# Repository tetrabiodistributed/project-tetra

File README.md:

# Project Tetra - Project Repository
This repository contains STL files and schematics for Project Tetra.

Project documentation available at https://tetrabiodistributed.github.io/docs

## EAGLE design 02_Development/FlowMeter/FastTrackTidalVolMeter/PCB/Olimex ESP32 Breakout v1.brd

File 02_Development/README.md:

READ ME

File for designs of the part in all stages, 
draft, final, in testing, 

PLEASE LABEL THE DESIGNS WITH THE STATUS AND VERSION.

PLEASE CREATE A PULL REQUEST FOR EACH DESIGN OF SPLITTER

MAIN FOCUS:

TEST RESULTS NEEDED

dimensions of tubing, if they fit

strength

flow

test with different lung sizes and compliances

flow rates to diff patients

TO DESIGN ensure fittings are ISO

device at the mouth to measure tidal flow, pressure,tidal volume

antiviral & antibacterial filter - integrated into design but not essential for operation

regulator of max pressure into lungs

PEEP valve connector

3 way valve formpatiemt isolation

On git with files please create a text/pdf documentation

Thread specs: ALL IN 3/8" NPT PLEASE

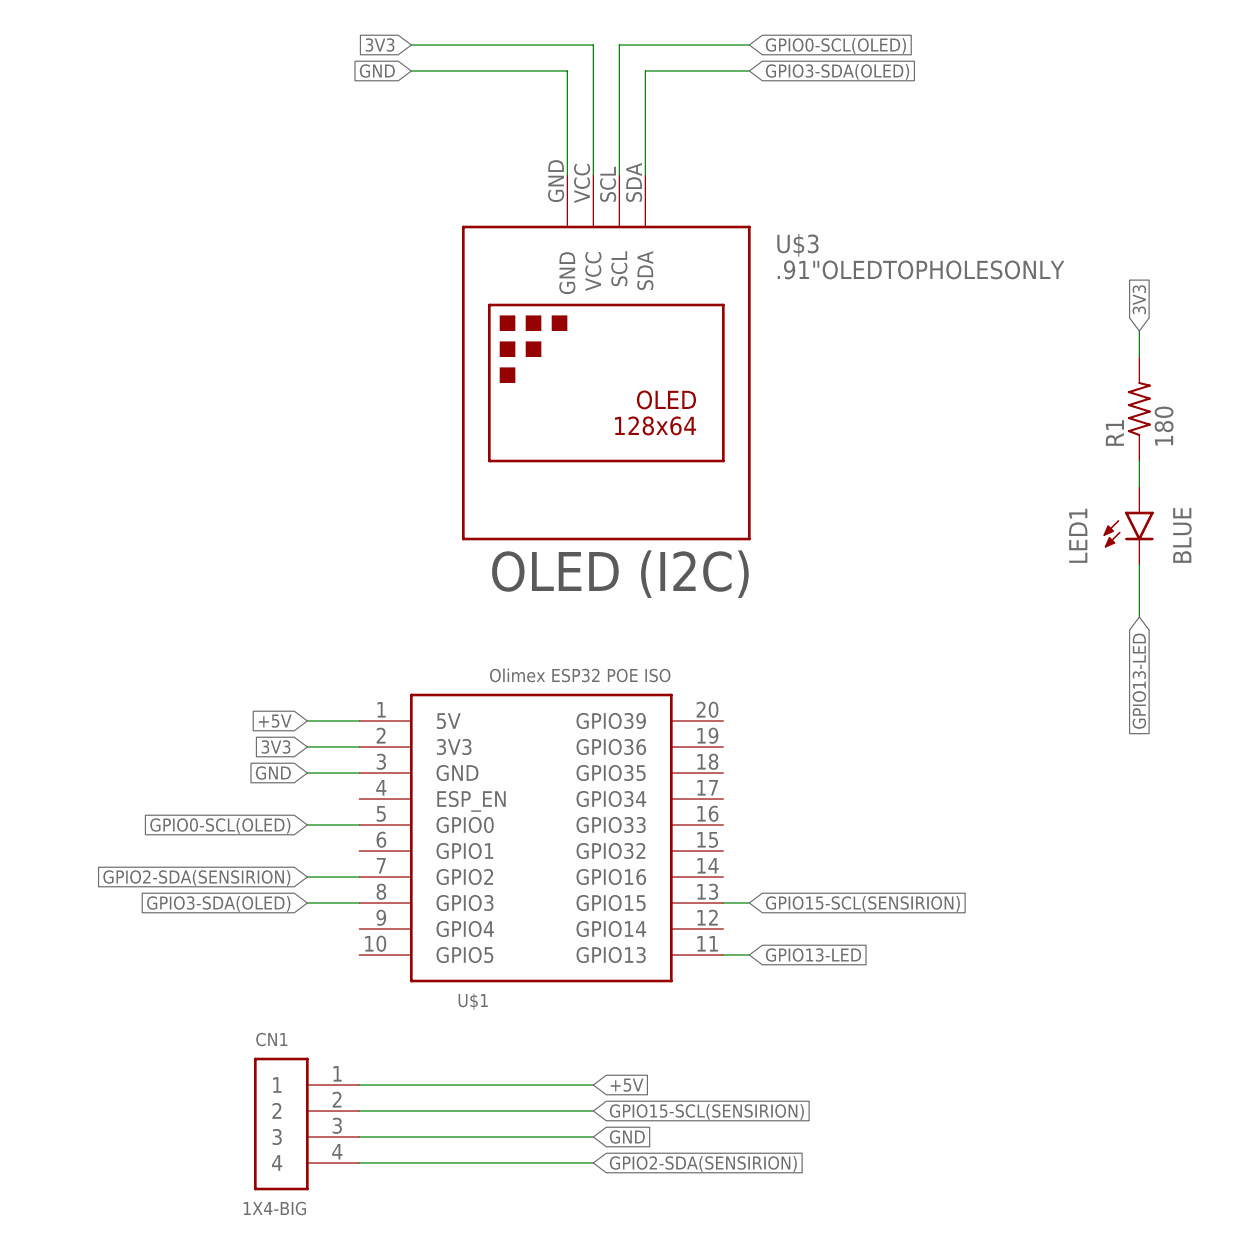
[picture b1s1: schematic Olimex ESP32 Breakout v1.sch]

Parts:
CN1: 1X4-BIG; 1X04-BIG
LED1: BLUE; LED-1206
R1: 180; R0805
U$1: OLIMEX_POE_ISOPOEISO; OLIMEX_POE_ISO
U$3: .91"OLEDTOPHOLESONLY; .96"OLED-TOPHOLESONLY

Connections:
3V3: R1.2, U$1.2 (3V3), U$3.VCC
+5V: CN1.1, U$1.1 (5V)
BLUEX: LED1.A, R1.1
GND: CN1.3, U$1.3 (GND), U$3.GND
GPIO0-SCL(OLED): U$1.5 (GPIO0), U$3.SCL
GPIO2-SDA(SENSIRION): CN1.4, U$1.7 (GPIO2)
GPIO3-SDA(OLED): U$1.8 (GPIO3), U$3.SDA
GPIO13-LED: LED1.C, U$1.11 (GPIO13)
GPIO15-SCL(SENSIRION): CN1.2, U$1.13 (GPIO15)

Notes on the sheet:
OLED (I2C)

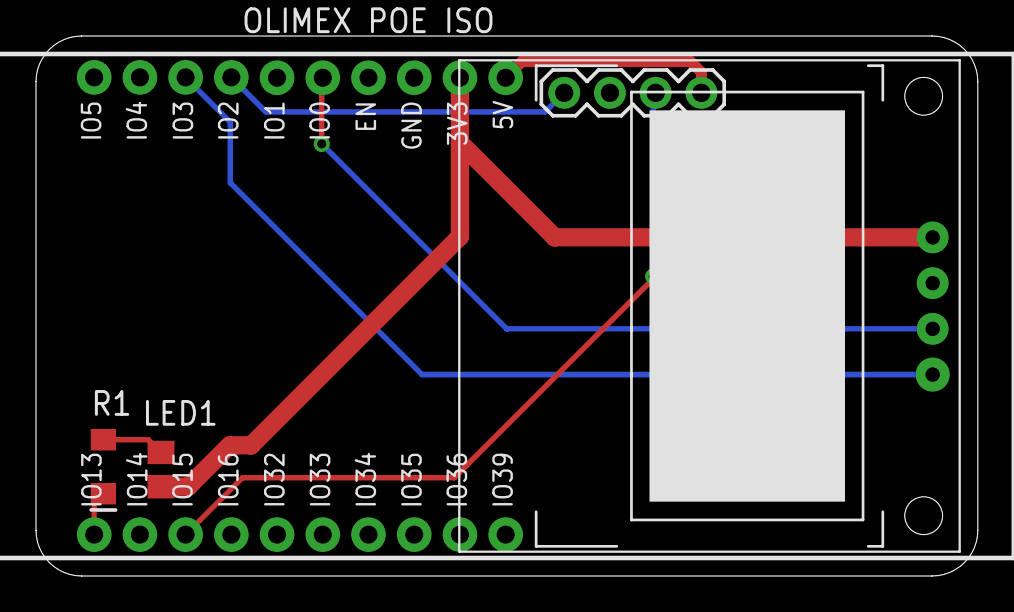
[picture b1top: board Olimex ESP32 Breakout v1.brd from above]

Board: 2 copper layers, 52.3 x 30.0 mm, 5 parts (0 on the bottom side), 9 nets.

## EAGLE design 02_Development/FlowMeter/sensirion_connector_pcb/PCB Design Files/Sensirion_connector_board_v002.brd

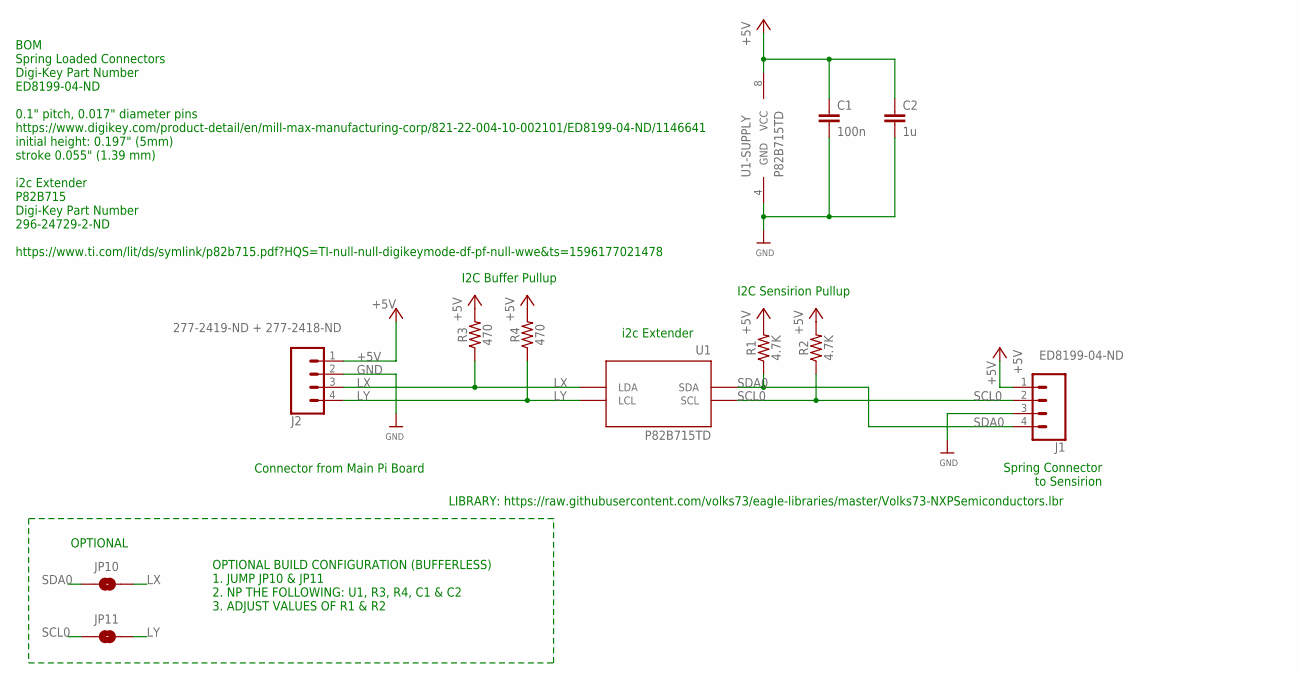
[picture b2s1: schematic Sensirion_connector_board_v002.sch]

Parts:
C1: 100n; 0805
C2: 1u; 0805
J1: ED8199-04-ND; 1X04_30MILL_DIA
J2: 277-2419-ND + 277-2418-ND; 1X04_3.5MM_RA
JP10, JP11: JUMPER-SMT_2_NO_SILK; SMT-JUMPER_2_NO_SILK
R1, R2: 4.7K; 0805
R3, R4: 470; 0805
U1: P82B715TD; SOIC-8

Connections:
+5V: C1.1, C2.1, J1.1, J2.1, R1.2, R2.2, R3.2, R4.2, U1.8 (VCC)
GND: C1.2, C2.2, J1.3, J2.2, U1.4 (GND)
LX: J2.3, JP10.2, R3.1, U1.7 (LDA)
LY: J2.4, JP11.2, R4.1, U1.2 (LCL)
SCL0: J1.2, JP11.1, R2.1, U1.3 (SCL)
SDA0: J1.4, JP10.1, R1.1, U1.6 (SDA)

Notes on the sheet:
Connector from Main Pi Board
BOM Spring Loaded Connectors Digi-Key Part Number ED8199-04-ND 0.1" pitch, 0.017" diameter pins https://www.digikey.com/product-detail/en/mill-max-manufacturing-corp/821-22-004-10-002101/ED8199-04-ND/1146641 initial height: 0.197" (5mm) stroke 0.055" (1.39 mm) i2c Extender P82B715 Digi-Key Part Num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
Spring Connector to Sensirion
OPTIONAL
i2c Extender
I2C Buffer Pullup
I2C Sensirion Pullup
OPTIONAL BUILD CONFIGURATION (BUFFERLESS) 1. JUMP JP10 & JP11 2. NP THE FOLLOWING: U1, R3, R4, C1 & C2 3. ADJUST VALUES OF R1 & R2
LIBRARY: https://raw.githubusercontent.com/volks73/eagle-libraries/master/Volks73-NXPSemiconductors.lbr

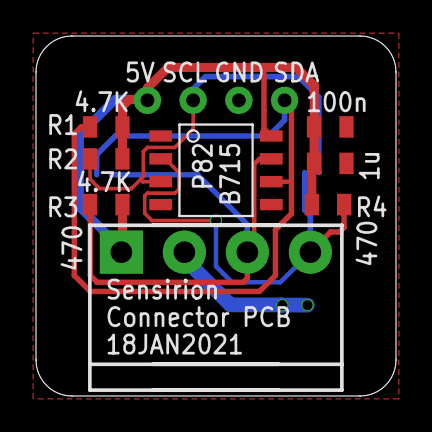
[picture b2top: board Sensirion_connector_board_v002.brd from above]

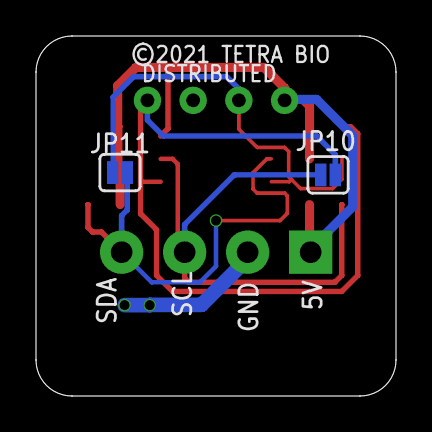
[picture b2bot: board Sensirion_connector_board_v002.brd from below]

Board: 2 copper layers, 20.0 x 20.0 mm, 11 parts (2 on the bottom side), 6 nets.

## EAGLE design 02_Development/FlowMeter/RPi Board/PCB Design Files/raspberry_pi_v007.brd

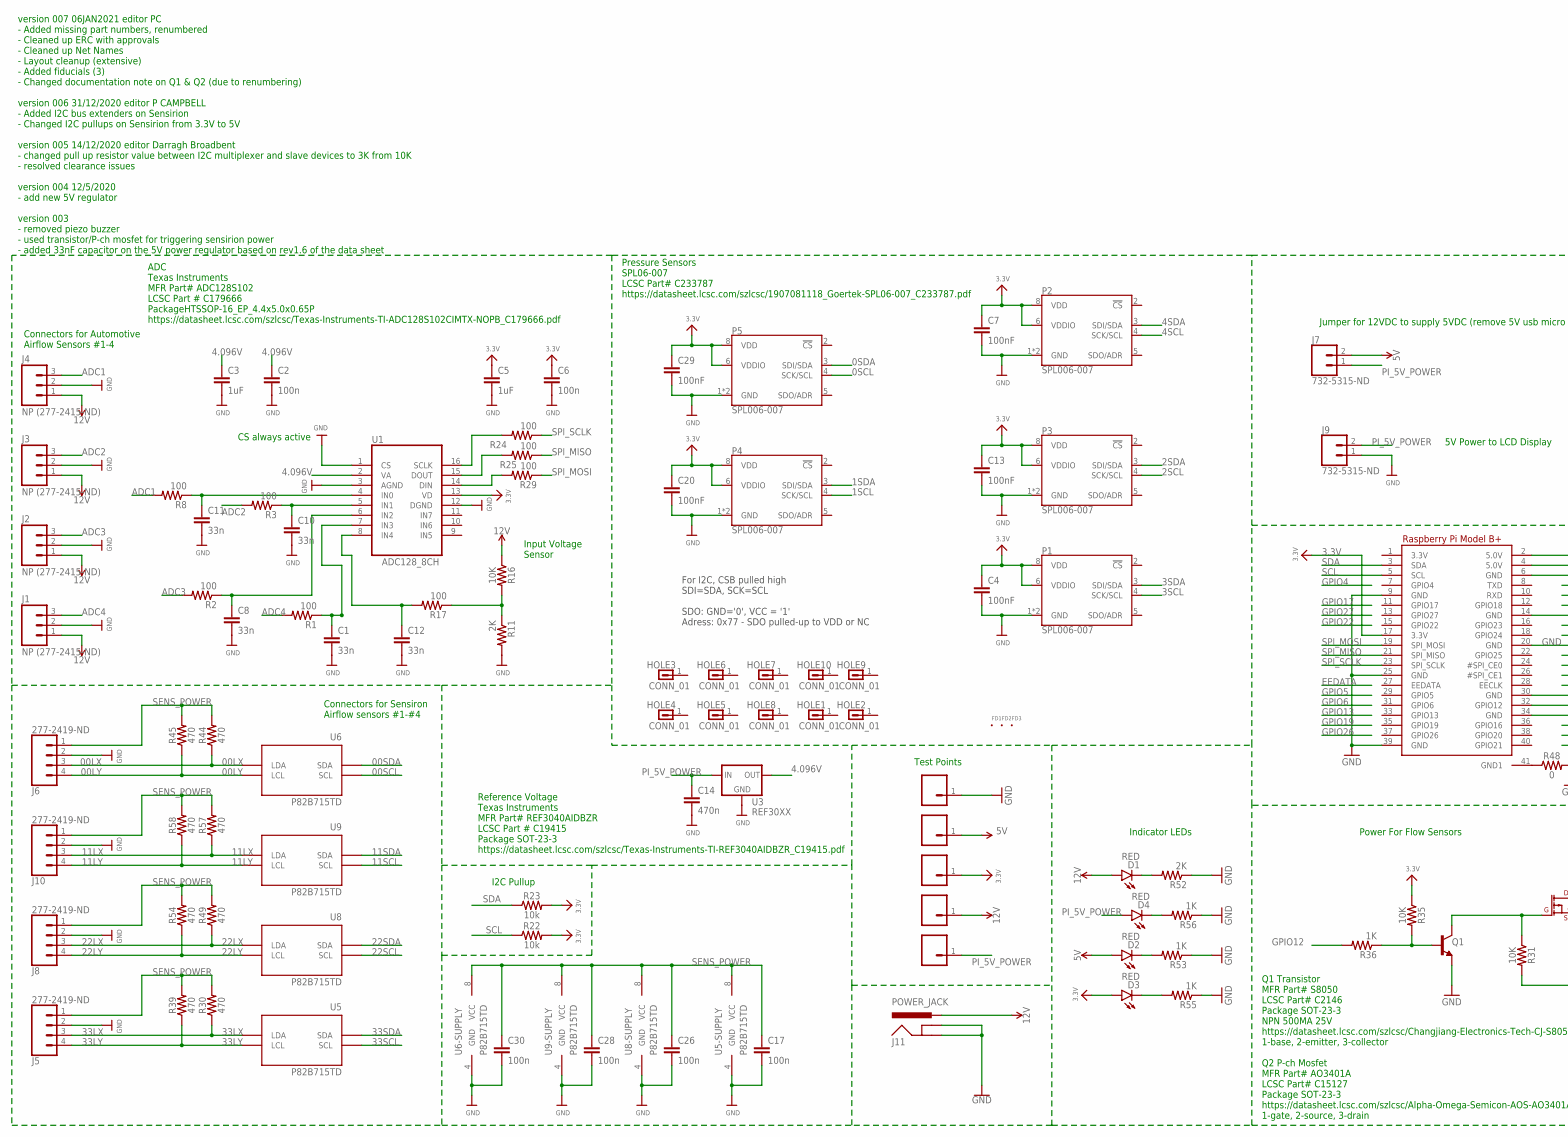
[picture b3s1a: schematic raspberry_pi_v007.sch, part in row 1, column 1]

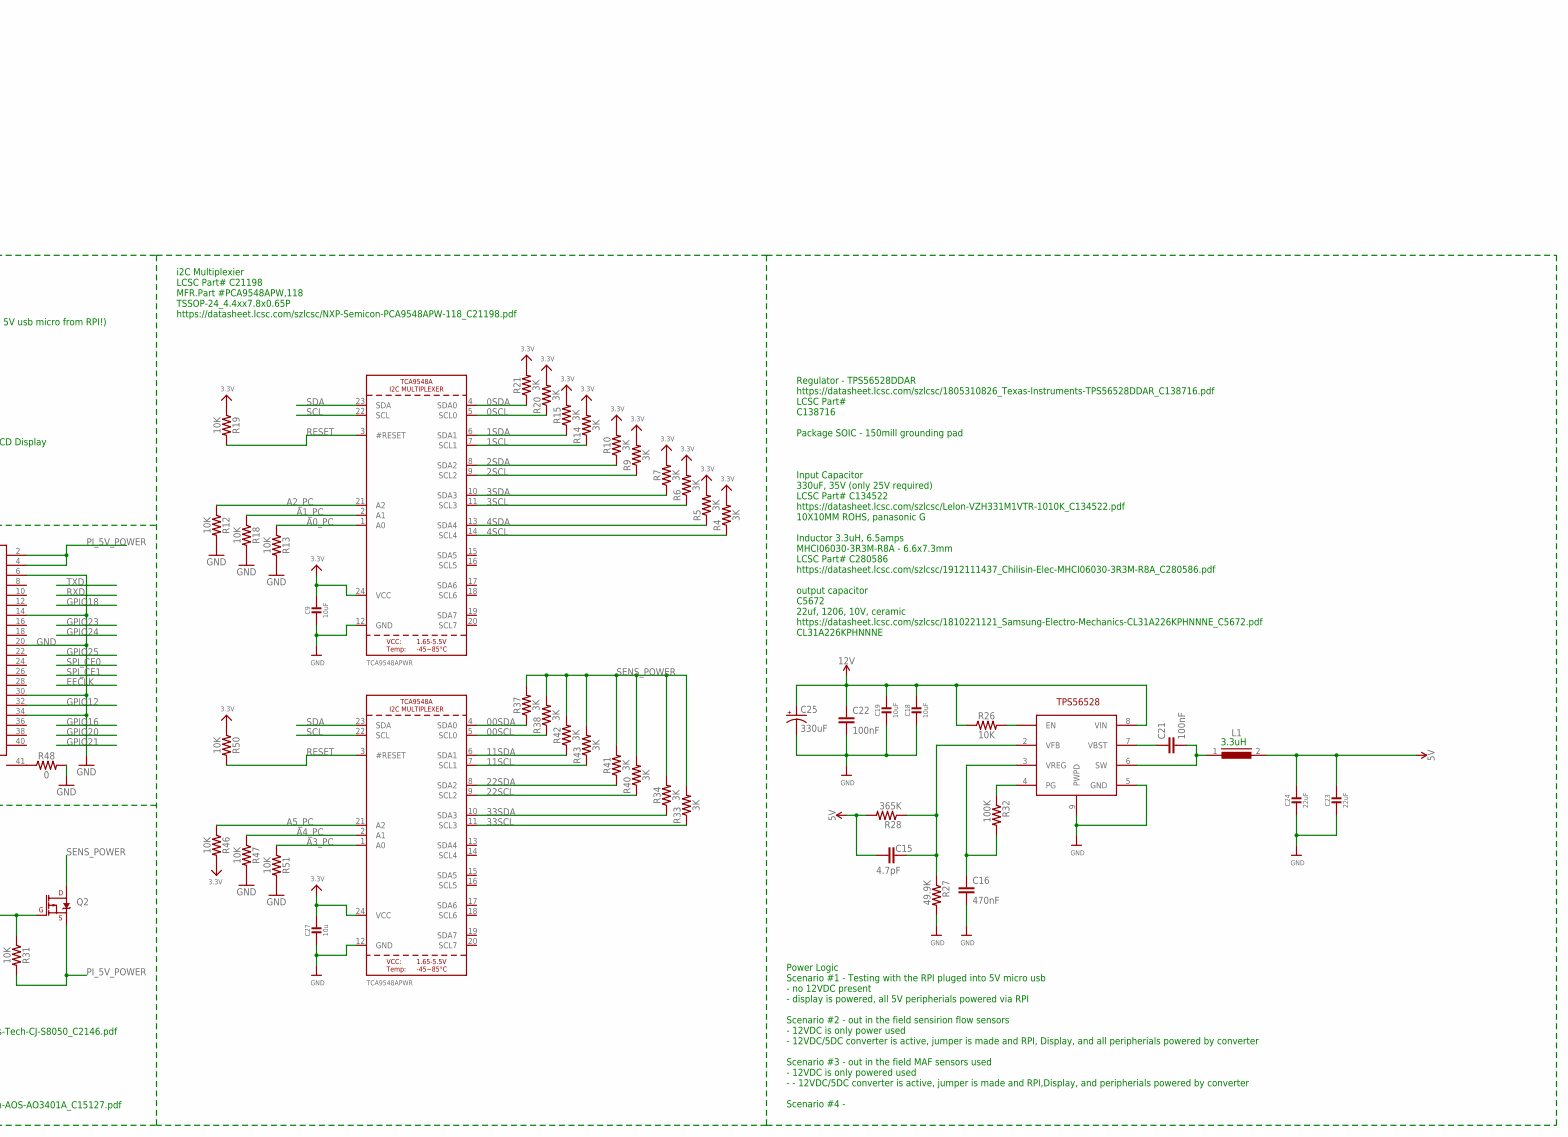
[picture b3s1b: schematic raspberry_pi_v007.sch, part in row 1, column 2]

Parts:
C1, C8, C10, C11, C12: 33n; 0805
C2, C6, C17, C26, C28, C30: 100n; 0805
C3, C5: 1uF; 0805
C4, C7, C13, C20, C21, C22, C29: 100nF; 0805
C9, C18, C19: 10uF; 0805-NO
C14: 470n; 0805
C15: 4.7pF; 0603
C16: 470nF; 0805
C23, C24: 22uF; _1206
C25: 330uF; PANASONIC_G
C27: 10u; 0805-NO
D1, D2, D3, D4: RED; LED-1206
FD1, FD2, FD3: FID_40MIL; FID_040
HOLE1, HOLE2, HOLE3, HOLE4, HOLE5, HOLE6, HOLE7, HOLE8, HOLE9, HOLE10: CONN_01; 1X01-#6_MACHINE
J1, J2, J3, J4: NP (277-2415-ND); SCREWTERMINAL-3.5MM-3
J5, J6, J8, J10: 277-2419-ND; 1X04_3.5MM_RA
J7: 732-5315-ND; 1X02
J9: 732-5315-ND; SCREWTERMINAL-5MM-2
J11: POWER_JACK; POWER_JACK_PTH
L1: INDUCTOR_6.6_7.3
P1, P2, P3, P4, P5: SPL006-007; LGA-8-2.5X2.0
Q1: 500mA/300V; SOT23-3
Q2: 4.3A/20V/54mΩ; SOT23-3
R1, R2, R3, R8, R17, R24, R25, R29: 100; 0805
R4, R5, R6, R7, R9, R10, R14, R15, R20, R21, R33, R34, R37, R38, R40, R41, R42, R43: 3K; 0805
R11, R52: 2K; 0805
R12, R13, R16, R18, R19, R26, R31, R35, R46, R47, R50, R51: 10K; 0805
R22, R23: 10k; 0805
R27: 49.9K; 0805
R28: 365K; 0805
R30, R39, R44, R45, R49, R54, R57, R58: 470; 0805
R32: 100K; 0805
R36, R53, R55, R56: 1K; 0805
R48: 0; 0805
RPI3B+: MICROBUILDER_RASPBERRYPI_BPLUS_HATSLOTS; MICROBUILDER_PI_HAT_SLOTS
TP1, TP2, TP3, TP4, TP5: CONN_0138MILL; 1X01-40MILL
U1: ADC128_8CH; TSSOP16
U2, U7: TCA9548APWR; TSSOP24
U3: REF30XX; SOT23-3
U4: TPS56528; SOIC8_POWER
U5, U6, U8, U9: P82B715TD; SOIC-8

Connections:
00LX: J6.3, R44.1, U6.7 (LDA)
00LY: J6.4, R45.1, U6.2 (LCL)
0SCL: P5.4 (SCK/SCL), R20.1, U2.5 (SCL0)
00SCL: R38.1, U6.3 (SCL), U7.5 (SCL0)
0SDA: P5.3 (SDI/SDA), R21.1, U2.4 (SDA0)
00SDA: R37.1, U6.6 (SDA), U7.4 (SDA0)
1SCL: P4.4 (SCK/SCL), R14.1, U2.7 (SCL1)
1SDA: P4.3 (SDI/SDA), R15.1, U2.6 (SDA1)
2SCL: P3.4 (SCK/SCL), R9.1, U2.9 (SCL2)
2SDA: P3.3 (SDI/SDA), R10.1, U2.8 (SDA2)
3.3V: C4.1, C5.1, C6.1, C7.1, C9.1, C13.1, C20.1, C27.1, C29.1, D3.A, P1.6 (VDDIO), P1.8 (VDD), P2.6 (VDDIO), P2.8 (VDD), P3.6 (VDDIO), P3.8 (VDD), P4.6 (VDDIO), P4.8 (VDD), P5.6 (VDDIO), P5.8 (VDD), R4.2, R5.2, R6.2, R7.2, R9.2, R10.2, R14.2, R15.2, R19.1, R20.2, R21.2, R22.2, R23.2, R35.1, R46.2, R50.1, RPI3B+.17 (3.3V), TP4.1, U1.13 (VD), U2.24 (VCC), U7.24 (VCC)
3.3V-LED-R: D3.C, R55.2
3SCL: P1.4 (SCK/SCL), R6.1, U2.11 (SCL3)
3SDA: P1.3 (SDI/SDA), R7.1, U2.10 (SDA3)
4.096V: C2.1, C3.1, U1.2 (VA), U3.2 (OUT)
4SCL: P2.4 (SCK/SCL), R4.1, U2.14 (SCL4)
4SDA: P2.3 (SDI/SDA), R5.1, U2.13 (SDA4)
5V: C15.1, C23.1, C24.1, D2.A, J7.2, L1.2, R28.2, TP2.1; also elsewhere on the board
5V-LED-R: D2.C, R53.2
5VREG-EN: R26.2, U4.1 (EN)
5VREG-PG: R32.1, U4.4 (PG)
5VREG-SW: C21.2, L1.1, U4.6 (SW)
5VREG-VBST: C21.1, U4.7 (VBST)
5VREG-VFB: C15.2, R27.1, R28.1, U4.2 (VFB)
5VREG-VREG: C16.1, R32.2, U4.3 (VREG)
11LX: J10.3, R57.1, U9.7 (LDA)
11LY: J10.4, R58.1, U9.2 (LCL)
11SCL: R43.1, U7.7 (SCL1), U9.3 (SCL)
11SDA: R42.1, U7.6 (SDA1), U9.6 (SDA)
12V: C18.1, C19.1, C22.1, C25.+, D1.A, J1.1, J2.1, J3.1, J4.1, J11.PWR, R16.1, R26.1, TP1.1, U4.8 (VIN)
12V-LED-R: D1.C, R52.2
22LX: J8.3, R49.1, U8.7 (LDA)
22LY: J8.4, R54.1, U8.2 (LCL)
22SCL: R40.1, U7.9 (SCL2), U8.3 (SCL)
22SDA: R41.1, U7.8 (SDA2), U8.6 (SDA)
33LX: J5.3, R30.1, U5.7 (LDA)
33LY: J5.4, R39.1, U5.2 (LCL)
33SCL: R33.1, U5.3 (SCL), U7.11 (SCL3)
33SDA: R34.1, U5.6 (SDA), U7.10 (SDA3)
A0_PC: R13.1, U2.1 (A0)
A1_PC: R18.1, U2.2 (A1)
A2_PC: R12.1, U2.21 (A2)
A3_PC: R51.1, U7.1 (A0)
A4_PC: R47.1, U7.2 (A1)
A5_PC: R46.1, U7.21 (A2)
ADC1: J4.3, R8.2
ADC2: J3.3, R3.2
ADC3: J2.3, R2.2
ADC4: J1.3, R1.2
ADC-12V-SENSE: R11.1, R16.2, R17.1
ADC-DIN: R29.2, U1.14 (DIN)
ADC-DOUT: R25.2, U1.15 (DOUT)
ADC-IN0: C11.1, R8.1, U1.4 (IN0)
ADC-IN1: C10.1, R3.1, U1.5 (IN1)
ADC-IN2: C8.1, R2.1, U1.6 (IN2)
ADC-IN3: C1.1, R1.1, U1.7 (IN3)
ADC-IN4: C12.1, R17.2, U1.8 (IN4)
ADC-SCLK: R24.2, U1.16 (SCLK)
GND: C1.2, C2.2, C3.2, C4.2, C5.2, C6.2, C7.2, C8.2, C9.2, C10.2, C11.2, C12.2, C13.2, C14.2, C16.2, C17.2, C18.2, C19.2, C20.2, C22.2, C23.2, C24.2, C25.-, C26.2, C27.2, C28.2, C29.2, C30.2, J1.2, J2.2, J3.2, J4.2, J5.2, J6.2, J8.2, J9.1, J10.2, J11.GND, J11.GNDBREAK, P1.1 (GND), P1.7 (GND), P2.1 (GND), P2.7 (GND), P3.1 (GND), P3.7 (GND), P4.1 (GND), P4.7 (GND), P5.1 (GND), P5.7 (GND), Q1.2 (E), R11.2, R12.2, R13.2, R18.2, R27.2, R47.2, R48.2, R51.2, R52.1, R53.1, R55.1, R56.1, RPI3B+.6 (GND), RPI3B+.9 (GND), RPI3B+.14 (GND), RPI3B+.20 (GND), RPI3B+.25 (GND), RPI3B+.30 (GND), RPI3B+.34 (GND), RPI3B+.39 (GND), TP3.1, U1.1 (CS), U1.3 (AGND), U1.12 (DGND), U2.12 (GND), U3.3 (GND), U4.5 (GND), U4.9 (PWPD), U5.4 (GND), U6.4 (GND), U7.12 (GND), U8.4 (GND), U9.4 (GND)
GND1: R48.1, RPI3B+.41 (GND1)
GPIO12: R36.2, RPI3B+.32 (GPIO12)
PI5V-LED-R: D4.C, R56.2
PI_5V_POWER: C14.1, D4.A, J7.1, J9.2, Q2.2 (S), R31.2, RPI3B+.2 (5.0V), RPI3B+.4 (5.0V), TP5.1, U3.1 (IN); also elsewhere on the board
RESET: R19.2, R50.2, U2.3 (#RESET), U7.3 (#RESET)
SCL: R22.1, RPI3B+.5 (SCL), U2.22 (SCL), U7.22 (SCL)
SDA: R23.1, RPI3B+.3 (SDA), U2.23 (SDA), U7.23 (SDA)
SENS_POWER: C17.1, C26.1, C28.1, C30.1, J5.1, J6.1, J8.1, J10.1, Q2.3 (D), R30.2, R33.2, R34.2, R37.2, R38.2, R39.2, R40.2, R41.2, R42.2, R43.2, R44.2, R45.2, R49.2, R54.2, R57.2, R58.2, U5.8 (VCC), U6.8 (VCC), U8.8 (VCC), U9.8 (VCC)
SENS_POWER_BASE: Q1.1 (B), R35.2, R36.1
SENS_POWER_GATE: Q1.3 (C), Q2.1 (G), R31.1
SPI_MISO: R25.1, RPI3B+.21 (SPI_MISO)
SPI_MOSI: R29.1, RPI3B+.19 (SPI_MOSI)
SPI_SCLK: R24.1, RPI3B+.23 (SPI_SCLK)

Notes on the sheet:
I2C Pullup
Test Points
Indicator LEDs
Power For Flow Sensors
For I2C, CSB pulled high SDI=SDA, SCK=SCL SDO: GND='0', VCC = '1' Adress: 0x77 - SDO pulled-up to VDD or NC
Connectors for Automotive Airflow Sensors #1-4
Pressure Sensors SPL06-007 LCSC Part# C233787 https://datasheet.lcsc.com/szlcsc/1907081118_Goertek-SPL06-007_C233787.pdf
Connectors for Sensiron Airflow sensors #1-#4
CS always active
Regulator - TPS56528DDAR https://datasheet.lcsc.com/szlcsc/1805310826_Texas-Instruments-TPS56528DDAR_C138716.pdf LCSC Part# C138716 Package SOIC - 150mill grounding pad Input Capacitor 330uF, 35V (only 25V required) LCSC Part# C134522 https://datasheet.lcsc.com/szlcsc/Lelon-VZH331M1VTR-1010K_C13452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
i2C Multiplexier LCSC Part# C21198 MFR.Part #PCA9548APW,118 TSSOP-24_4.4xx7.8x0.65P https://datasheet.lcsc.com/szlcsc/NXP-Semicon-PCA9548APW-118_C21198.pdf
ADC Texas Instruments MFR Part# ADC128S102 LCSC Part # C179666 PackageHTSSOP-16_EP_4.4x5.0x0.65P https://datasheet.lcsc.com/szlcsc/Texas-Instruments-TI-ADC128S102CIMTX-NOPB_C179666.pdf
Reference Voltage Texas Instruments MFR Part# REF3040AIDBZR LCSC Part # C19415 Package SOT-23-3 https://datasheet.lcsc.com/szlcsc/Texas-Instruments-TI-REF3040AIDBZR_C19415.pdf
Q1 Transistor MFR Part# S8050 LCSC Part# C2146 Package SOT-23-3 NPN 500MA 25V https://datasheet.lcsc.com/szlcsc/Changjiang-Electronics-Tech-CJ-S8050_C2146.pdf 1-base, 2-emitter, 3-collector Q2 P-ch Mosfet MFR Part# AO3401A LCSC Part# C15127 Package SOT-23-3 https://datasheet.lcsc.com/szlcsc/Alpha-O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
Input Voltage Sensor
Jumper for 12VDC to supply 5VDC (remove 5V usb micro from RPI!)
5V Power to LCD Display
Power Logic Scenario #1 - Testing with the RPI pluged into 5V micro usb - no 12VDC present - display is powered, all 5V peripherials powered via RPI Scenario #2 - out in the field sensirion flow sensors - 12VDC is only power used - 12VDC/5DC converter is active, jumper is made and RPI, Display, and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
version 007 06JAN2021 editor PC - Added missing part numbers, renumbered - Cleaned up ERC with approvals - Cleaned up Net Names - Layout cleanup (extensive) - Added fiducials (3) - Changed documentation note on Q1 & Q2 (due to renumbering) version 006 31/12/2020 editor P CAMPBELL - Added I2C bus ex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
3.3uH

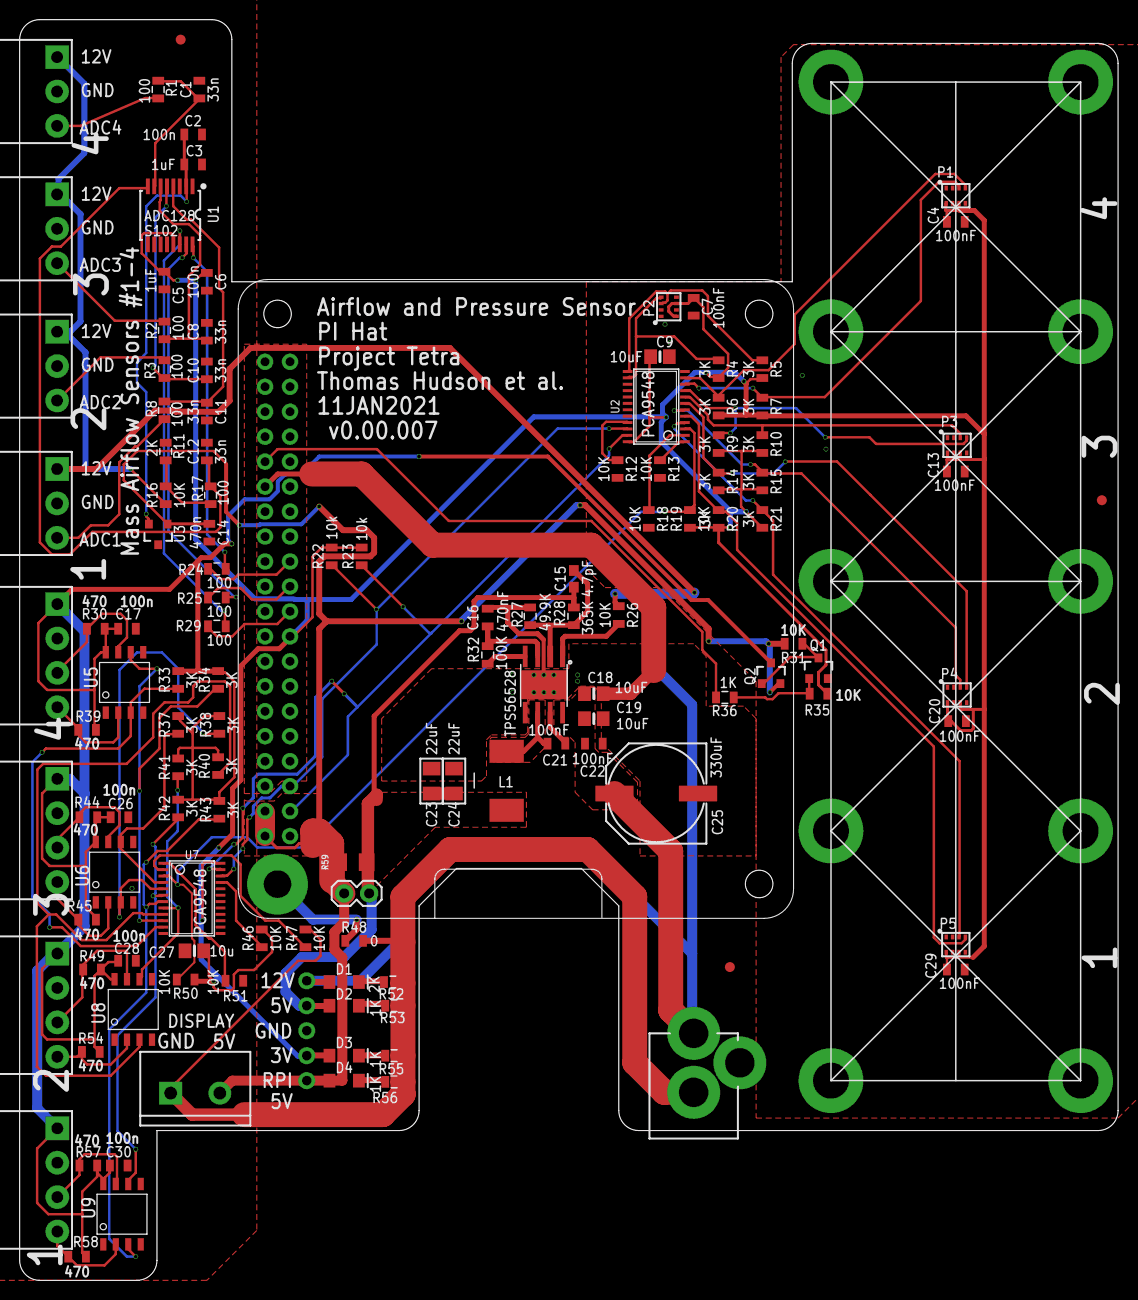
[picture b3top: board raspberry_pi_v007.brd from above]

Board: 2 copper layers, 111.8 x 128.3 mm, 140 parts (0 on the bottom side), 72 nets.

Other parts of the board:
R59: 0R; 1206

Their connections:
5V: R59.2; also elsewhere on the board
PI_5V_POWER: R59.1; also elsewhere on the board

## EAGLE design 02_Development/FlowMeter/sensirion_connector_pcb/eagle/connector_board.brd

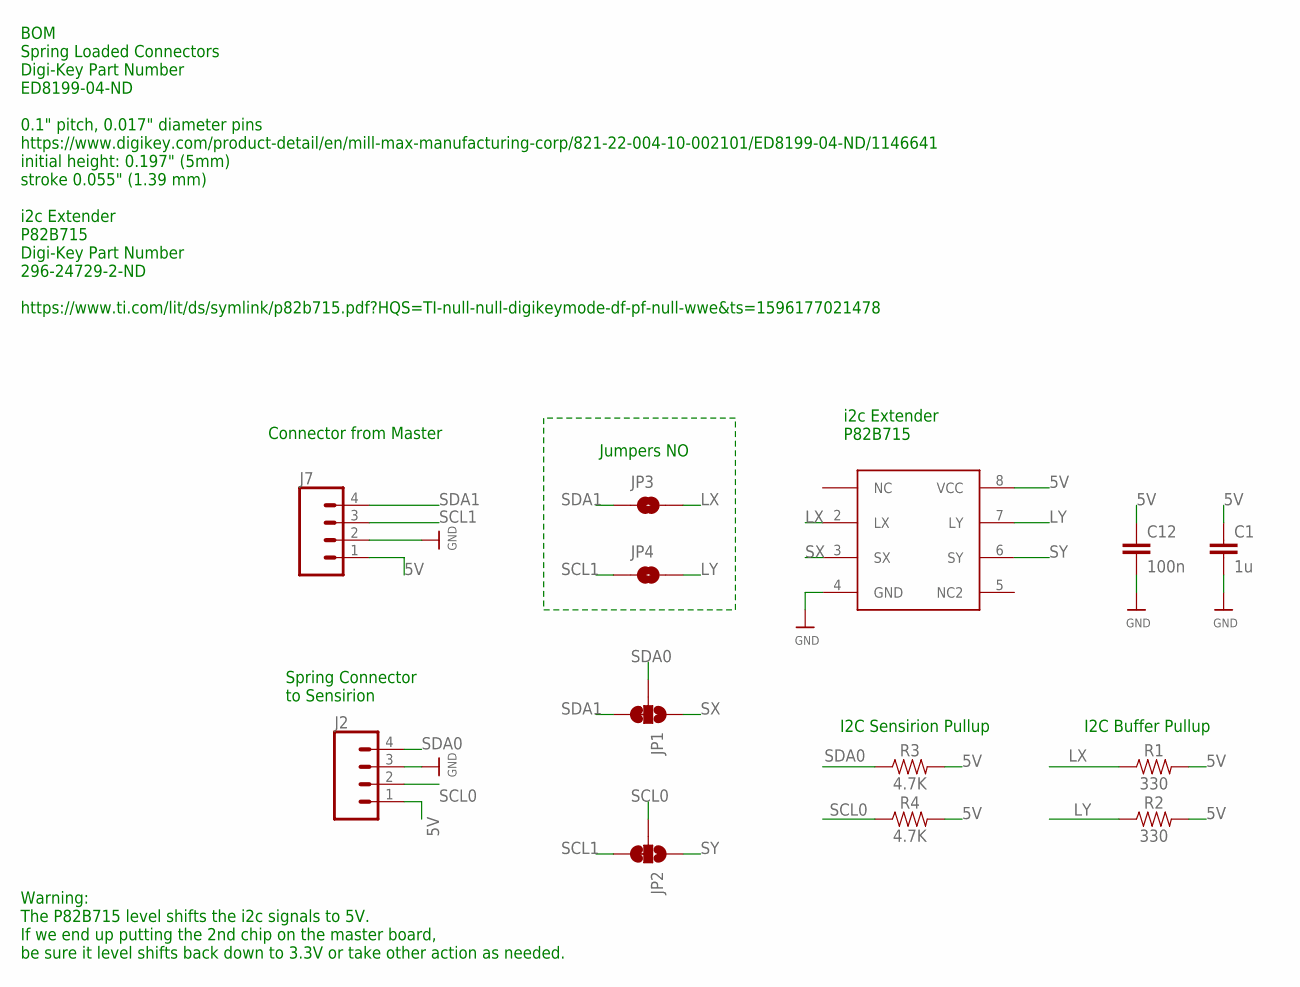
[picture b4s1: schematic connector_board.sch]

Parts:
C1: 1u; 0805
C12: 100n; 0805
J2: CONN_0430MILL_DIA; 1X04_30MILL_DIA
J7: CONN_043.5MM_RA; 1X04_3.5MM_RA
JP1, JP2: JUMPER-SMT_3_1-NC_TRACE_NO-SILK; SMT-JUMPER_3_1-NC_TRACE_NO-SILK
JP3, JP4: JUMPER-SMT_2_NO_SILK; SMT-JUMPER_2_NO_SILK
R1, R2: 330; 0805
R3, R4: 4.7K; 0805
U$2: P82B715; SOIC8

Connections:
5V: C1.1, C12.1, J2.1, J7.1, R1.2, R2.2, R3.2, R4.2, U$2.8 (VCC)
GND: C1.2, C12.2, J2.3, J7.2, U$2.4 (GND)
LX: JP3.2, R1.1, U$2.2 (LX)
LY: JP4.2, R2.1, U$2.7 (LY)
SCL0: J2.2, JP2.2, R4.1
SCL1: J7.3, JP2.3, JP4.1
SDA0: J2.4, JP1.2, R3.1
SDA1: J7.4, JP1.3, JP3.1
SX: JP1.1, U$2.3 (SX)
SY: JP2.1, U$2.6 (SY)

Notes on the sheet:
Connector from Master
BOM Spring Loaded Connectors Digi-Key Part Number ED8199-04-ND 0.1" pitch, 0.017" diameter pins https://www.digikey.com/product-detail/en/mill-max-manufacturing-corp/821-22-004-10-002101/ED8199-04-ND/1146641 initial height: 0.197" (5mm) stroke 0.055" (1.39 mm) i2c Extender P82B715 Digi-Key Part Num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
Warning: The P82B715 level shifts the i2c signals to 5V. If we end up putting the 2nd chip on the master board, be sure it level shifts back down to 3.3V or take other action as needed.
Spring Connector to Sensirion
Jumpers NO
i2c Extender P82B715
I2C Buffer Pullup
I2C Sensirion Pullup

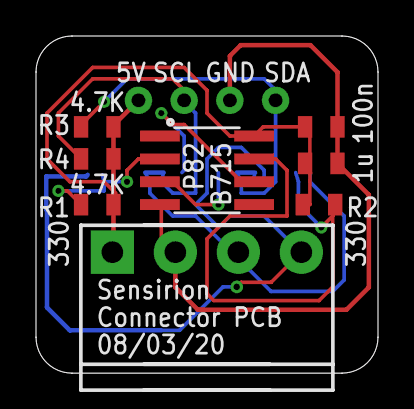
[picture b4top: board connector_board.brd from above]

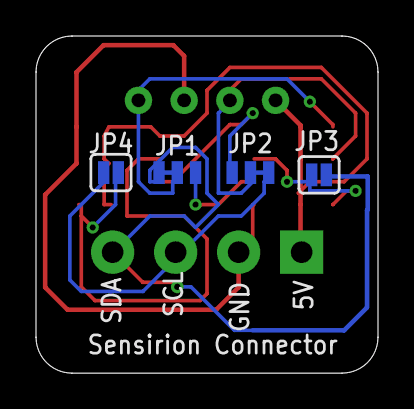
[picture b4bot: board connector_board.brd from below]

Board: 2 copper layers, 19.0 x 18.7 mm, 13 parts (4 on the bottom side), 10 nets.

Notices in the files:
02_Development/FlowMeter/sensirion_connector_pcb/PCB Design Files/Sensirion_connector_board_v002.brd:
©2021 TETRA BIO
parts and their libraries:
SparkFun-LED: Licensing: Creative Commons ShareAlike 4.0 International - https://creativecommons.org/licenses/by-sa/4.0
microbuilder: This work is placed in the public domain, and may be freely used for commercial and non-commercial work with the following conditions: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
